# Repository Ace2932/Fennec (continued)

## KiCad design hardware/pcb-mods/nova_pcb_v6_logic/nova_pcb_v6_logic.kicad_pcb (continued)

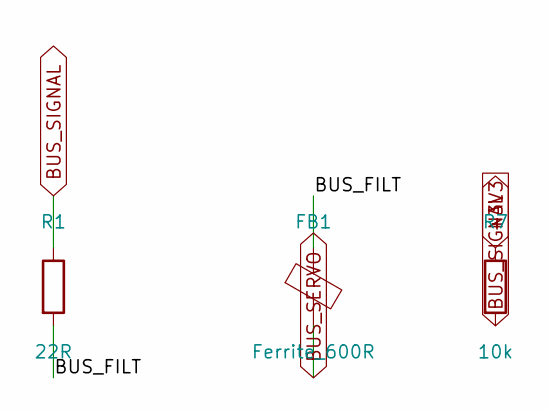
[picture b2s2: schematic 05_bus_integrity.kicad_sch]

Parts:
FB1: Ferrite_600R; L_0603_1608Metric
R1: 22R; R_0603_1608Metric
R7: 10k; R_0603_1608Metric

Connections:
+3V3: R7.1; also elsewhere on the board
/05 Bus Integrity/BUS_FILT: FB1.1, R1.2
BUS_SERVO: FB1.2; also elsewhere on the board
BUS_SIGNAL: R1.1, R7.2; also elsewhere on the board

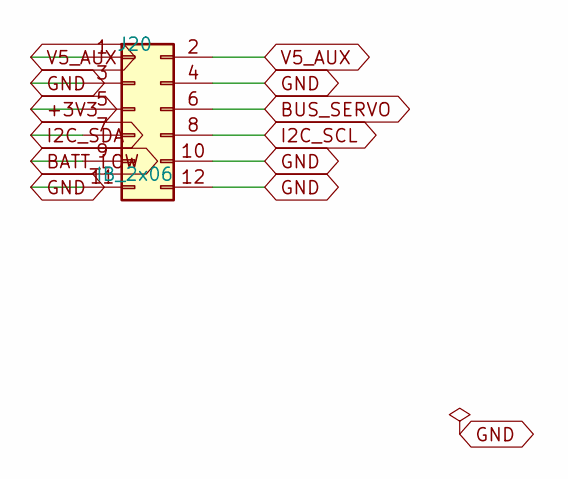
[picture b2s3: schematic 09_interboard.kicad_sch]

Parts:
J20: IB_2x06; IDC-Header_2x06_P2.54mm_Vertical

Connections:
+3V3: J20.5; also elsewhere on the board
BATT_LOW: J20.9; also elsewhere on the board
BUS_SERVO: J20.6; also elsewhere on the board
GND: J20.3, J20.4, J20.10, J20.11, J20.12; also elsewhere on the board
I2C_SCL: J20.8; also elsewhere on the board
I2C_SDA: J20.7; also elsewhere on the board
V5_AUX: J20.1, J20.2; also elsewhere on the board

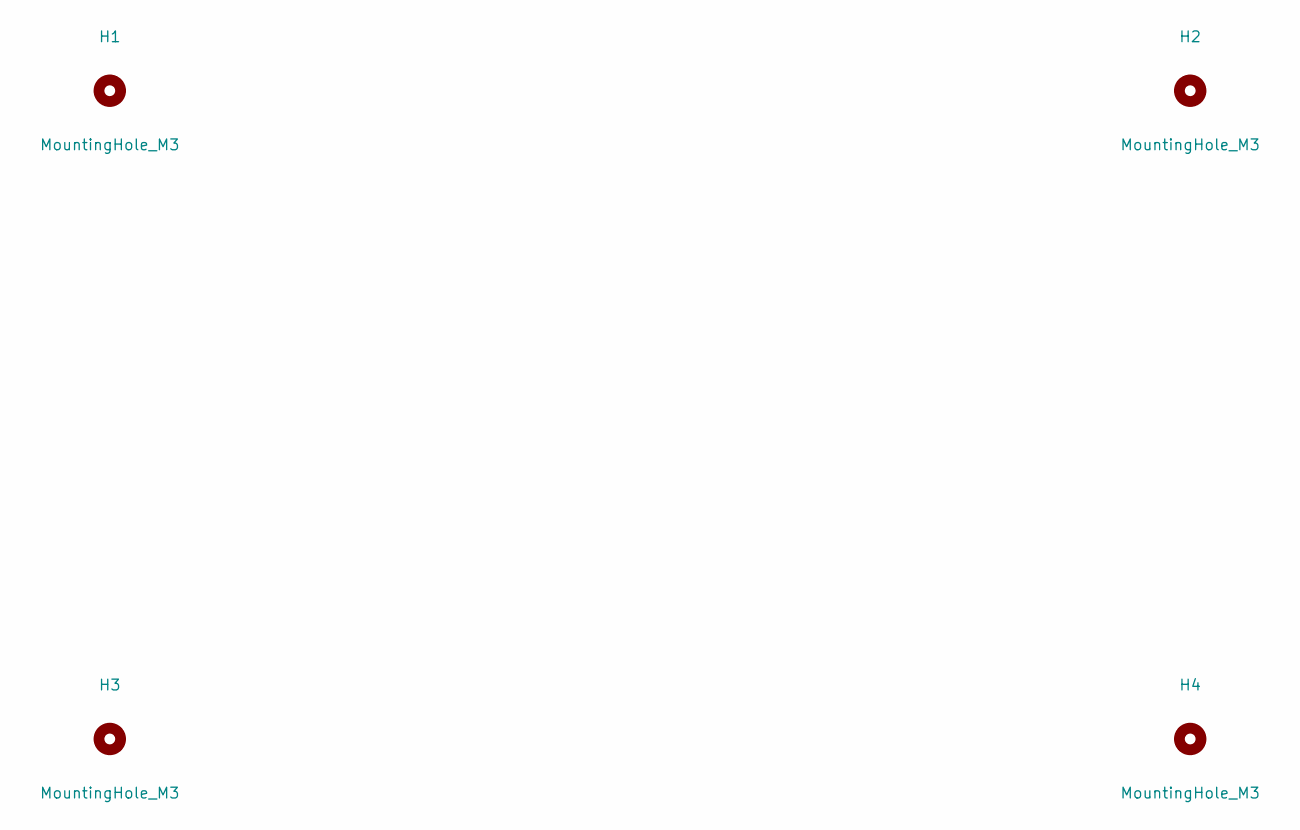
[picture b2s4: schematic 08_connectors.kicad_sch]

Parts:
H1, H2, H3, H4: MountingHole_M3; MountingHole_3.2mm_M3

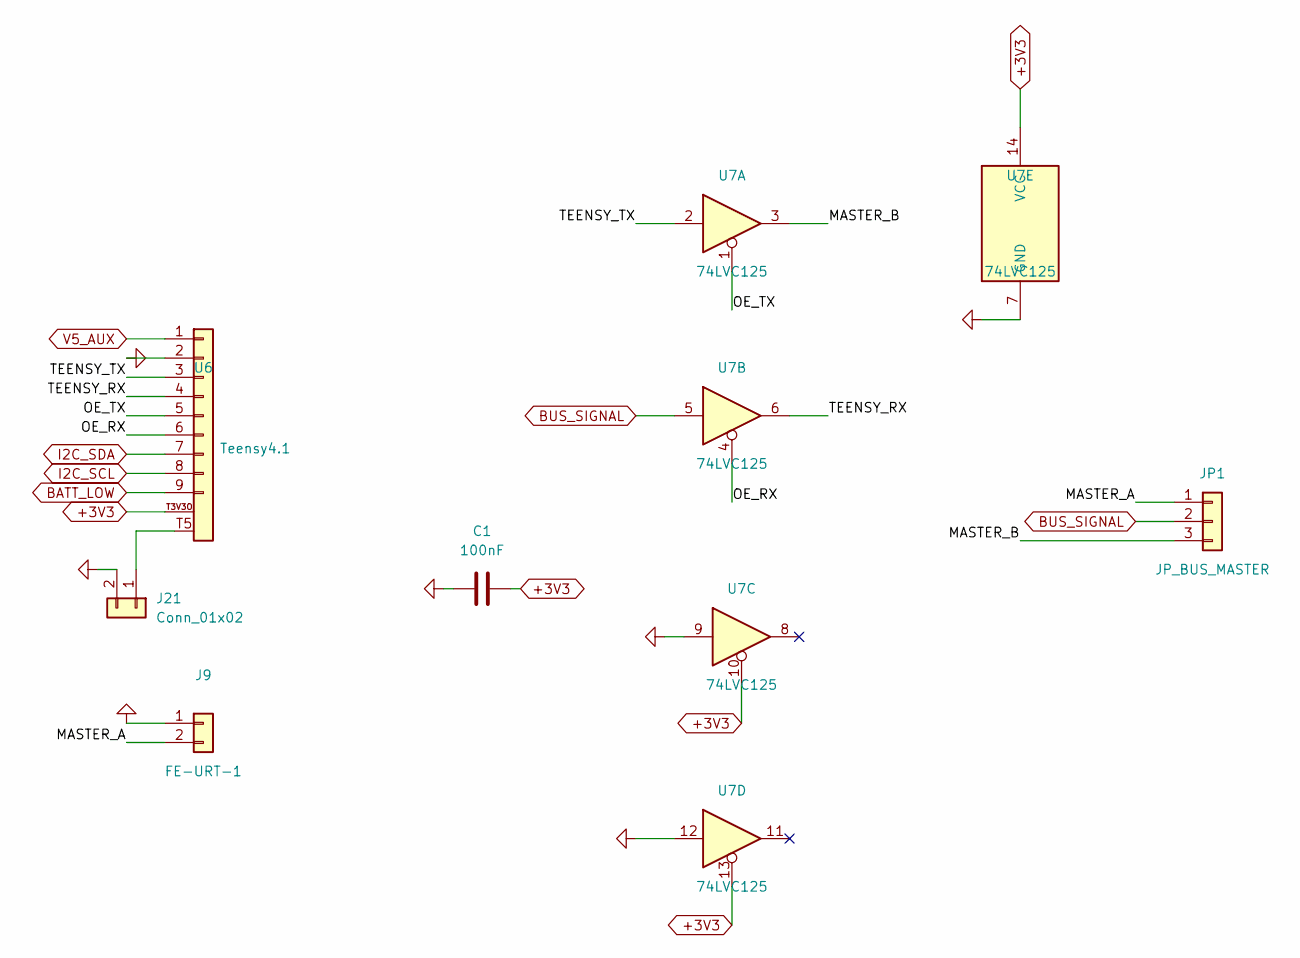
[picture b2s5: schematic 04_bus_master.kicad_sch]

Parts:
C1: 100nF; C_0603_1608Metric
J9: FE-URT-1; PinHeader_1x02_P2.54mm_Vertical
J21: Conn_01x02; PinHeader_1x02_P2.54mm_Vertical
JP1: JP_BUS_MASTER; PinHeader_1x03_P2.54mm_Vertical
U6: Teensy4.1; Teensy_4.1
U7: 74LVC125; SOIC-14_3.9x8.7mm_P1.27mm

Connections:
+3V3: C1.2, U6.T3V3O (3V3), U7.10, U7.13, U7.14 (VCC); also elsewhere on the board
/04 Bus Master (Pattern B)/MASTER_A: J9.2, JP1.1
/04 Bus Master (Pattern B)/MASTER_B: JP1.3, U7.3
/04 Bus Master (Pattern B)/OE_RX: U6.6, U7.4
/04 Bus Master (Pattern B)/OE_TX: U6.5, U7.1
/04 Bus Master (Pattern B)/TEENSY_RX: U6.4, U7.6
/04 Bus Master (Pattern B)/TEENSY_TX: U6.3, U7.2
BATT_LOW: U6.9; also elsewhere on the board
BUS_SIGNAL: JP1.2, U7.5; also elsewhere on the board
GND: C1.1, J9.1, J21.2, U6.2, U7.7 (GND), U7.9, U7.12; also elsewhere on the board
I2C_SCL: U6.8; also elsewhere on the board
I2C_SDA: U6.7; also elsewhere on the board
unnamed: J21.1, U6.T5
V5_AUX: U6.1; also elsewhere on the board

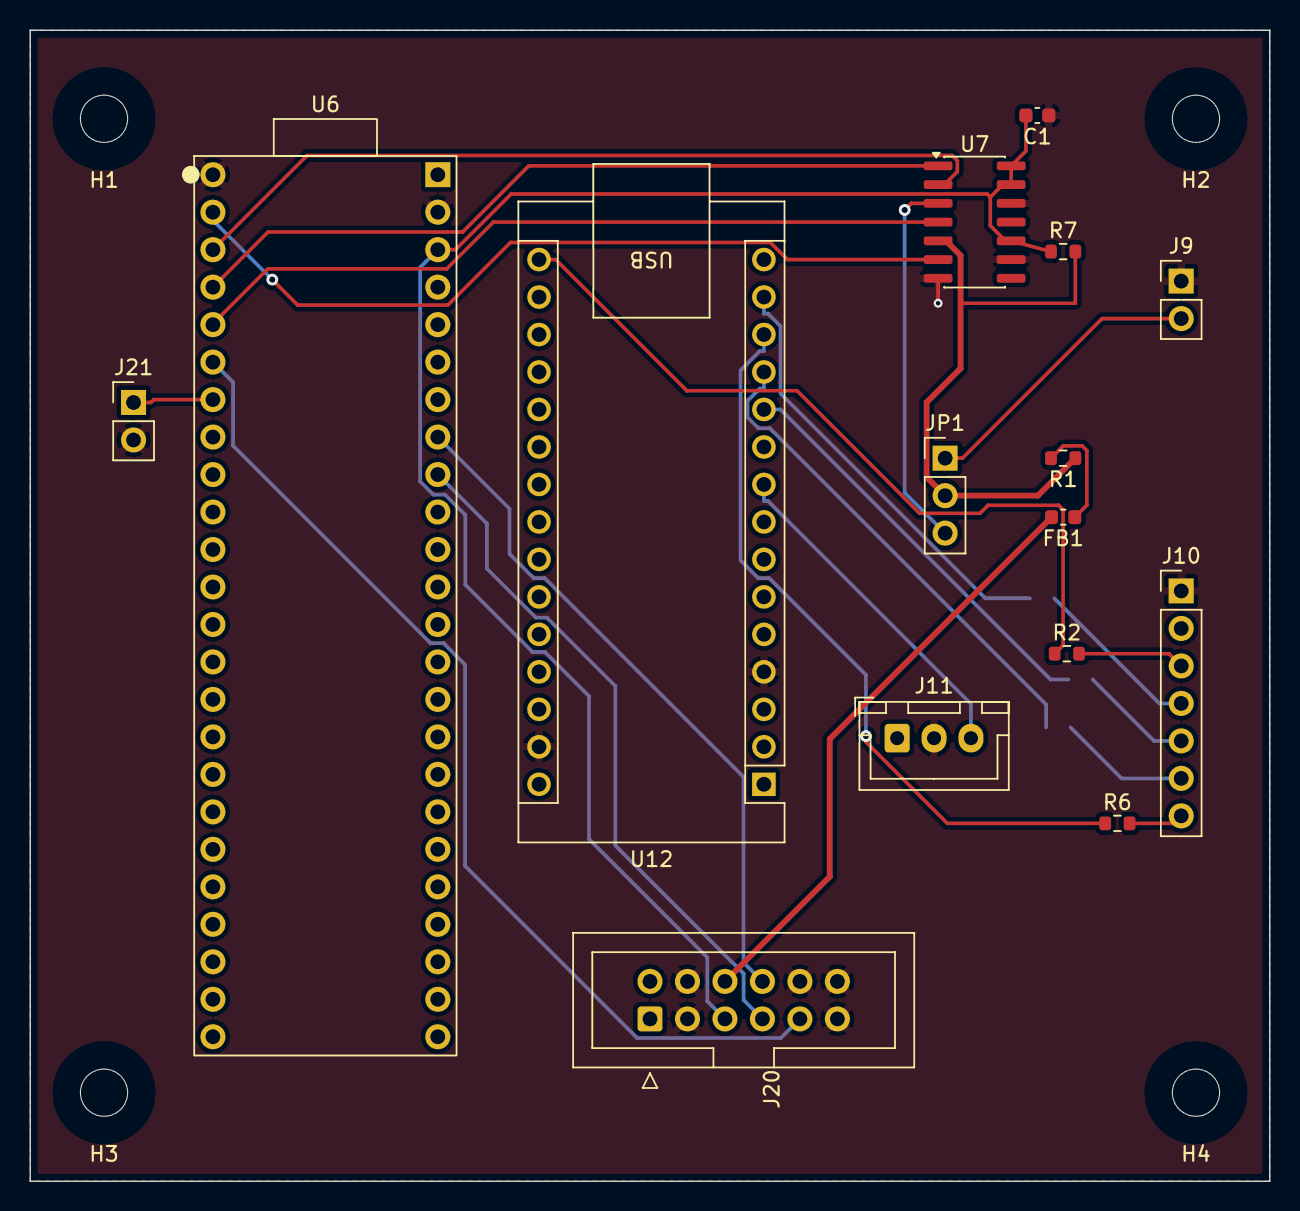
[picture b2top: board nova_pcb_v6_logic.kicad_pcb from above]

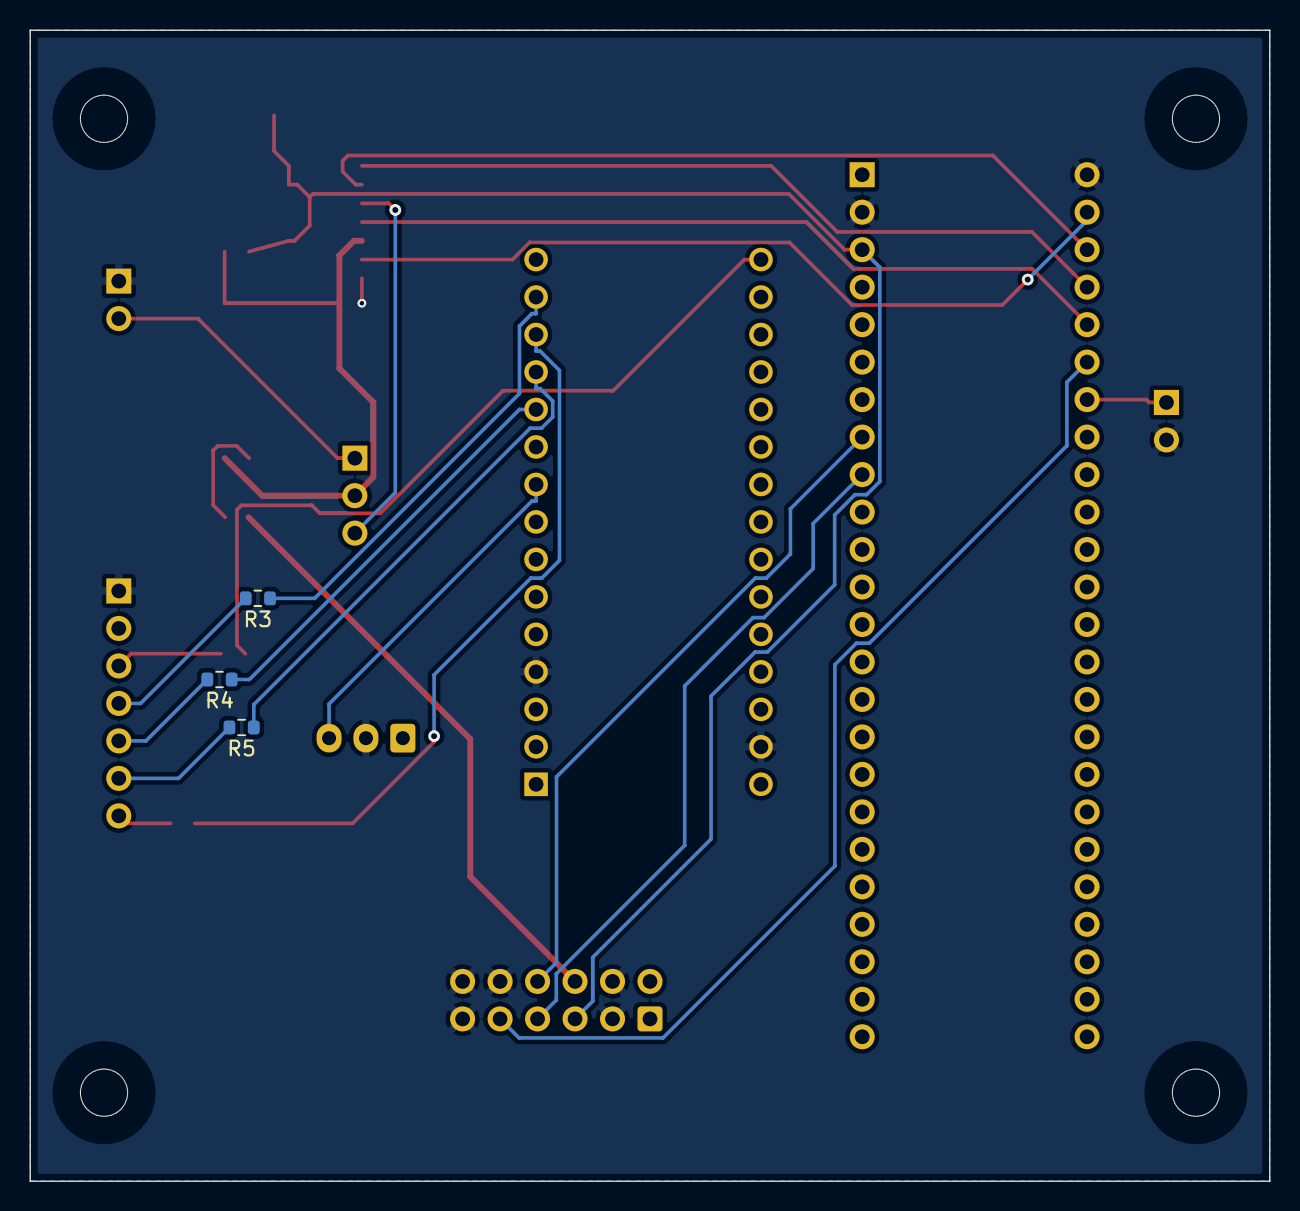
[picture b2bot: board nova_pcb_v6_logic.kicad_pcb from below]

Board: 4 copper layers, 84.0 x 78.0 mm, 22 parts (3 on the bottom side), 27 nets.

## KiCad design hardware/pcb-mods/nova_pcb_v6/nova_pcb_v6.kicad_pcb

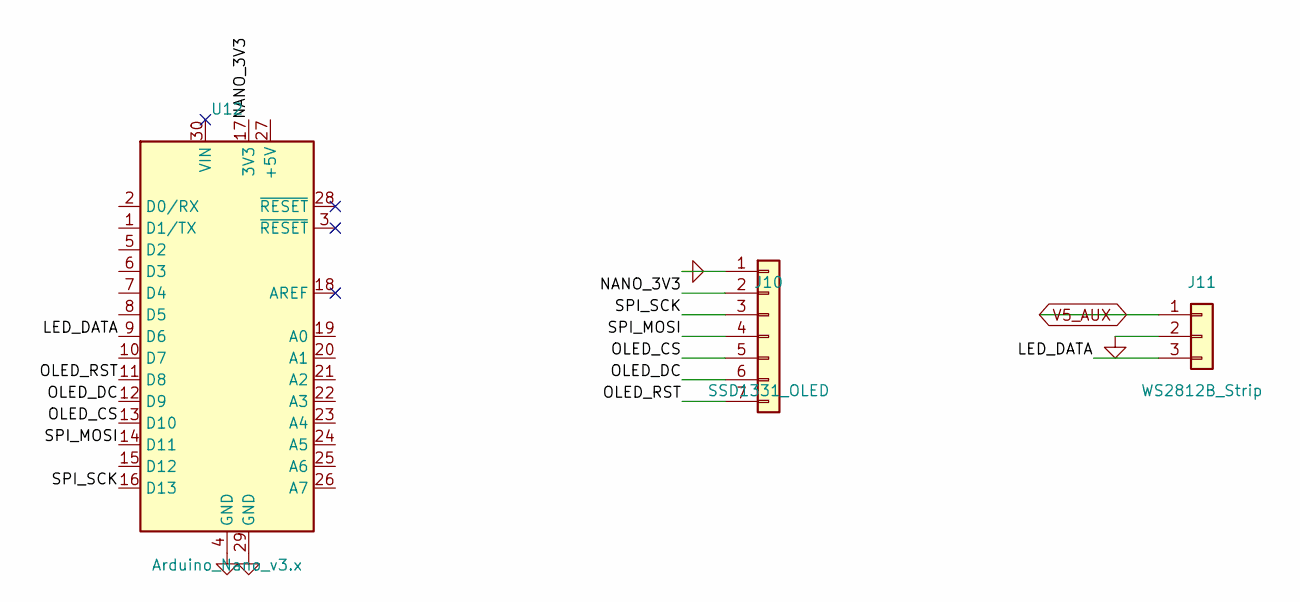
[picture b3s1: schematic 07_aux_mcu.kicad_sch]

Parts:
J10: SSD1331_OLED; PinHeader_1x07_P2.54mm_Vertical
J11: WS2812B_Strip; JST_XH_B3B-XH-A_1x03_P2.50mm_Vertical
U12: Arduino_Nano_v3.x; Arduino_Nano

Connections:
/07 Aux MCU + Peripherals/LED_DATA: J11.3, U12.9 (D6)
/07 Aux MCU + Peripherals/NANO_3V3: J10.2, U12.17 (3V3)
/07 Aux MCU + Peripherals/OLED_CS: J10.5, U12.13 (D10)
/07 Aux MCU + Peripherals/OLED_DC: J10.6, U12.12 (D9)
/07 Aux MCU + Peripherals/OLED_RST: J10.7, U12.11 (D8)
/07 Aux MCU + Peripherals/SPI_MOSI: J10.4, U12.14 (D11)
/07 Aux MCU + Peripherals/SPI_SCK: J10.3, U12.16 (D13)
GND: J10.1, J11.2, U12.4 (GND), U12.29 (GND); also elsewhere on the board
V5_AUX: J11.1; also elsewhere on the board

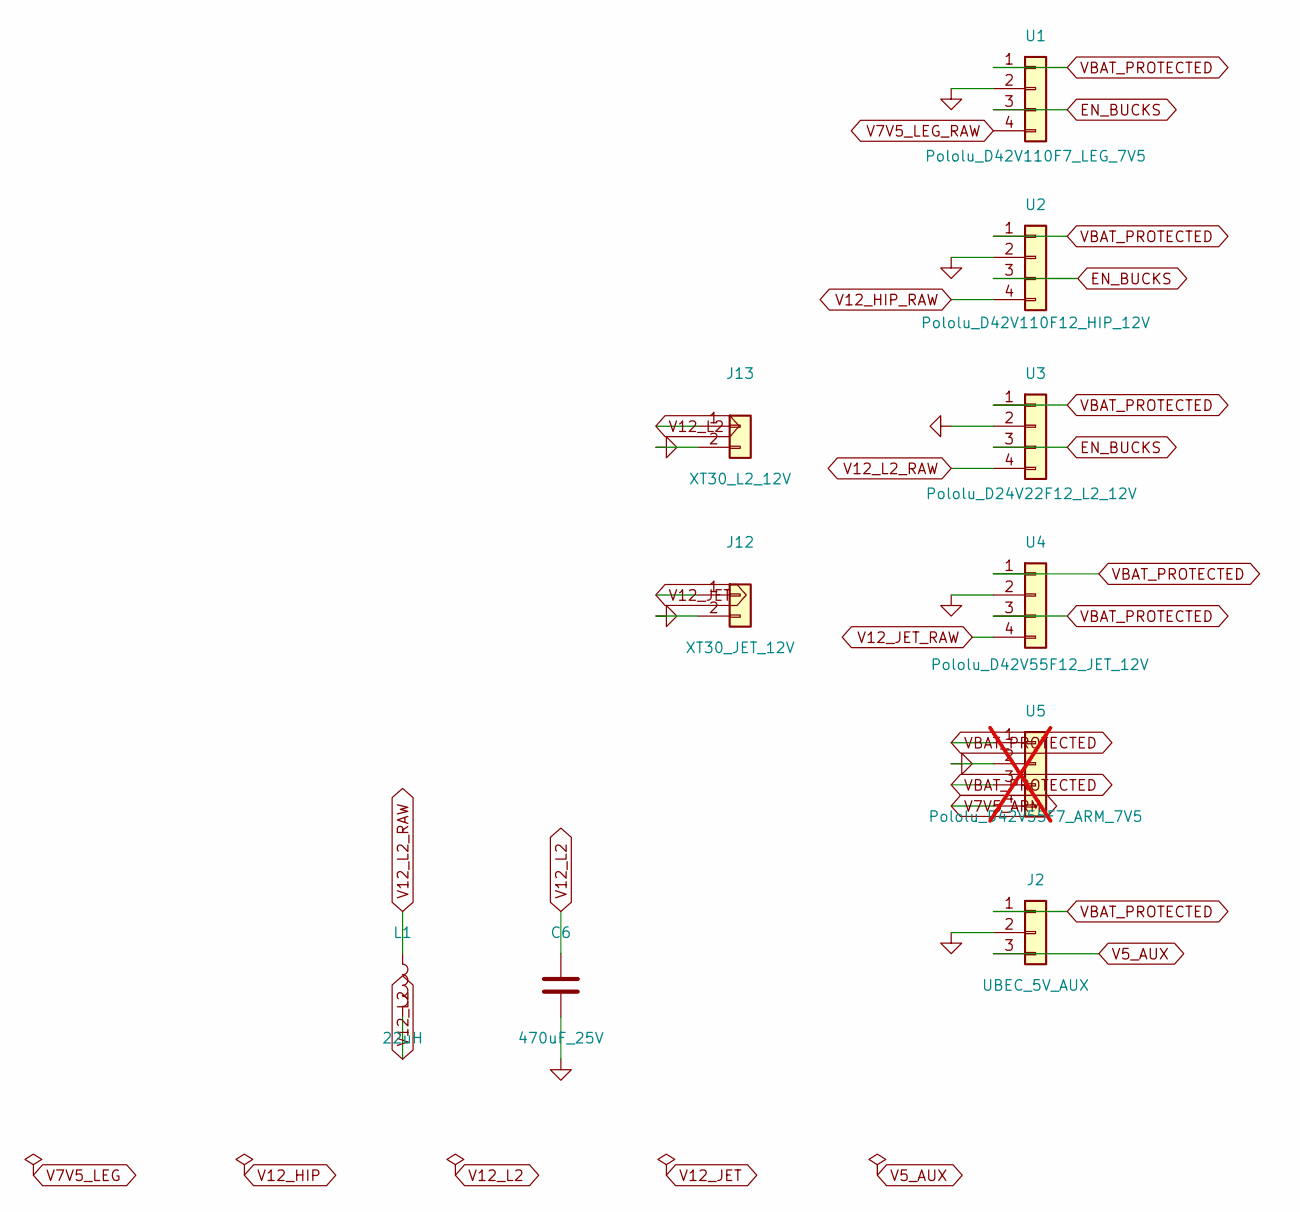
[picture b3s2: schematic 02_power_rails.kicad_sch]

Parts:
C6: 470uF_25V; CP_Radial_D10.0mm_P5.00mm
J2: UBEC_5V_AUX; PinHeader_1x03_P2.54mm_Vertical
J12: XT30_JET_12V; AMASS_XT30U-M_1x02_P5.0mm_Vertical
J13: XT30_L2_12V; AMASS_XT30U-M_1x02_P5.0mm_Vertical
L1: 22uH; L_12x12mm_H8mm
U1: Pololu_D42V110F7_LEG_7V5; Pololu_D42V110Fx
U2: Pololu_D42V110F12_HIP_12V; Pololu_D42V110Fx
U3: Pololu_D24V22F12_L2_12V; Pololu_D24V22Fx
U4: Pololu_D42V55F12_JET_12V; Pololu_D42V55Fx
U5: Pololu_D42V55F7_ARM_7V5; Pololu_D42V55Fx; not fitted

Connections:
EN_BUCKS: U1.3, U2.3, U3.3; also elsewhere on the board
GND: C6.2, J2.2, J12.2, J13.2, U1.2, U2.2, U3.2, U4.2, U5.2; also elsewhere on the board
V5_AUX: J2.3; also elsewhere on the board
V7V5_ARM: U5.4
V7V5_LEG_RAW: U1.4; also elsewhere on the board
V12_HIP_RAW: U2.4; also elsewhere on the board
V12_JET: J12.1; also elsewhere on the board
V12_JET_RAW: U4.4; also elsewhere on the board
V12_L2: C6.1, J13.1, L1.2
V12_L2_RAW: L1.1, U3.4
VBAT_PROTECTED: J2.1, U1.1, U2.1, U3.1, U4.1, U4.3, U5.1, U5.3; also elsewhere on the board

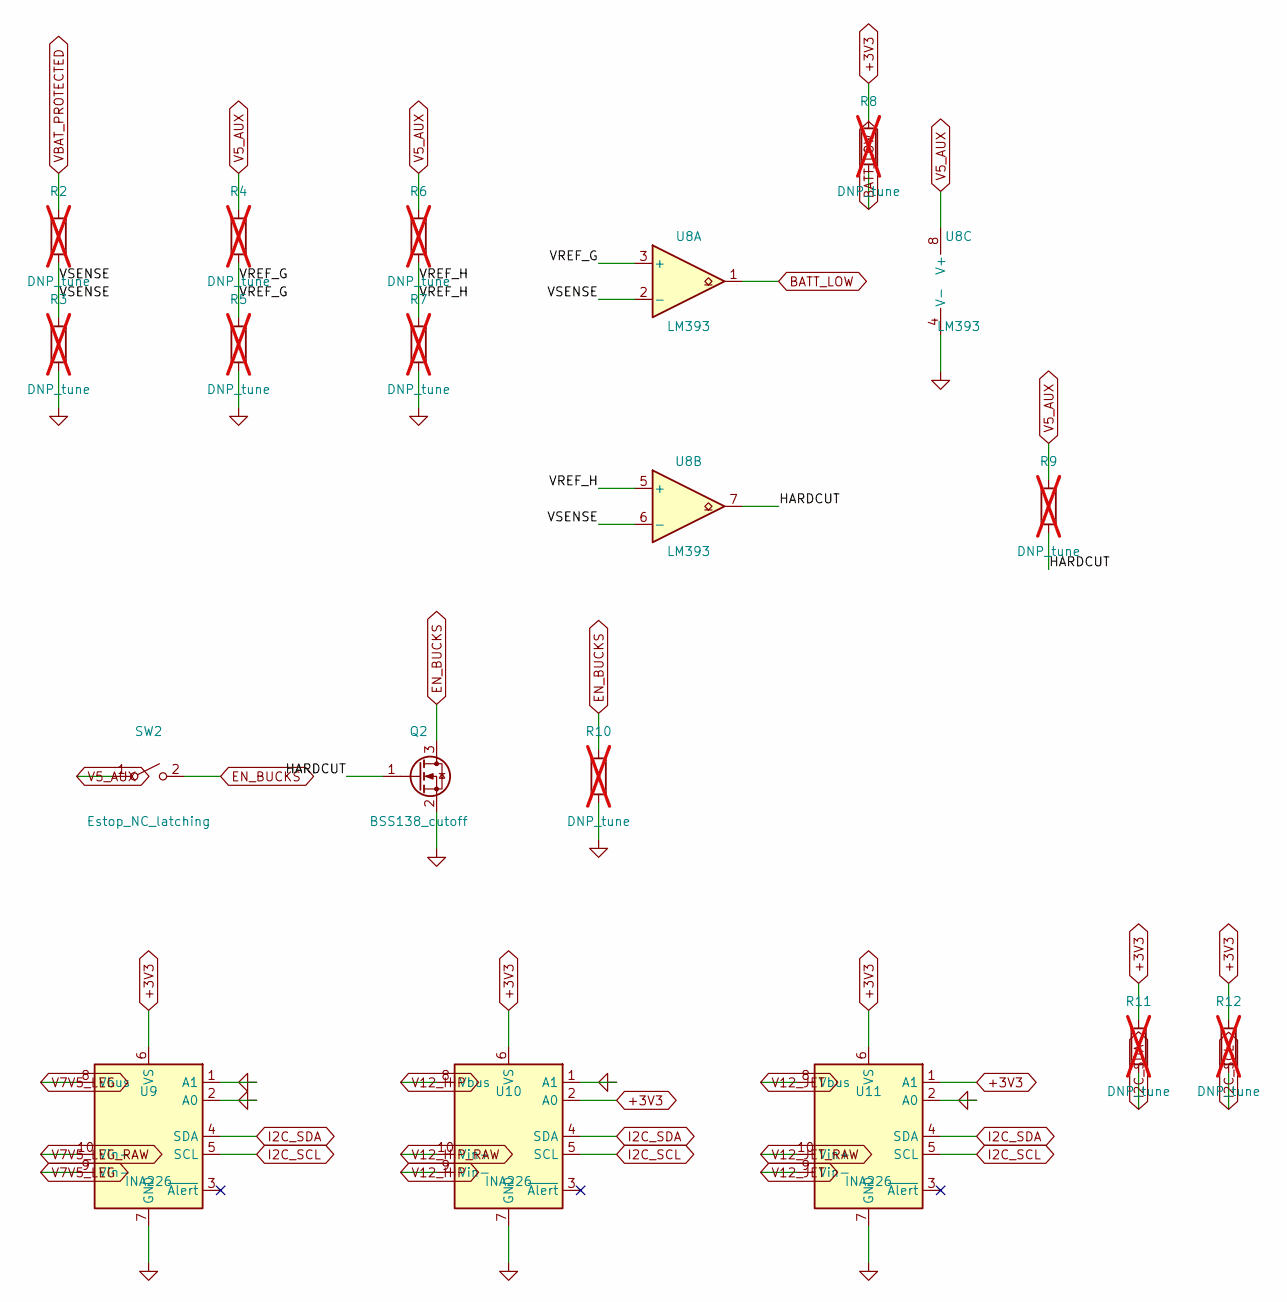
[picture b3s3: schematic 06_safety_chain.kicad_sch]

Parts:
Q2: BSS138_cutoff; SOT-23
R2, R3, R4, R5, R6, R7, R8, R9, R10, R11, R12: DNP_tune; R_0603_1608Metric; not fitted
SW2: Estop_NC_latching; TerminalBlock_Philmore_TB132_1x02_P5.00mm_Horizontal
U8: LM393; SOIC-8_3.9x4.9mm_P1.27mm
U9, U10, U11: INA226; INA226_Module_Breakout

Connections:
+3V3: R8.1, R11.1, R12.1, U9.6 (VS), U10.2 (A0), U10.6 (VS), U11.1 (A1), U11.6 (VS); also elsewhere on the board
/06 Safety Chain/HARDCUT: Q2.1 (G), R9.2, U8.7
/06 Safety Chain/VREF_G: R4.2, R5.1, U8.3 (+)
/06 Safety Chain/VREF_H: R6.2, R7.1, U8.5 (+)
/06 Safety Chain/VSENSE: R2.2, R3.1, U8.2 (-), U8.6 (-)
BATT_LOW: R8.2, U8.1; also elsewhere on the board
EN_BUCKS: Q2.3 (D), R10.1, SW2.2 (B); also elsewhere on the board
GND: Q2.2 (S), R3.2, R5.2, R7.2, R10.2, U8.4 (V-), U9.1 (A1), U9.2 (A0), U9.7 (GND), U10.1 (A1), U10.7 (GND), U11.2 (A0), U11.7 (GND); also elsewhere on the board
I2C_SCL: R12.2, U9.5 (SCL), U10.5 (SCL), U11.5 (SCL); also elsewhere on the board
I2C_SDA: R11.2, U9.4 (SDA), U10.4 (SDA), U11.4 (SDA); also elsewhere on the board
V5_AUX: R4.1, R6.1, R9.1, SW2.1 (A), U8.8 (V+); also elsewhere on the board
V7V5_LEG: U9.8 (Vbus), U9.9 (Vin-); also elsewhere on the board
V7V5_LEG_RAW: U9.10 (Vin+); also elsewhere on the board
V12_HIP: U10.8 (Vbus), U10.9 (Vin-); also elsewhere on the board
V12_HIP_RAW: U10.10 (Vin+); also elsewhere on the board
V12_JET: U11.8 (Vbus), U11.9 (Vin-); also elsewhere on the board
V12_JET_RAW: U11.10 (Vin+); also elsewhere on the board
VBAT_PROTECTED: R2.1; also elsewhere on the board

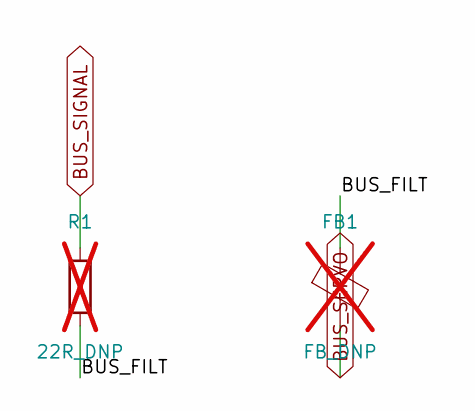
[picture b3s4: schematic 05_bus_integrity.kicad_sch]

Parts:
FB1: FB_DNP; L_0603_1608Metric; not fitted
R1: 22R_DNP; R_0603_1608Metric; not fitted

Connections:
/05 Bus Integrity/BUS_FILT: FB1.1, R1.2
BUS_SERVO: FB1.2; also elsewhere on the board
BUS_SIGNAL: R1.1; also elsewhere on the board

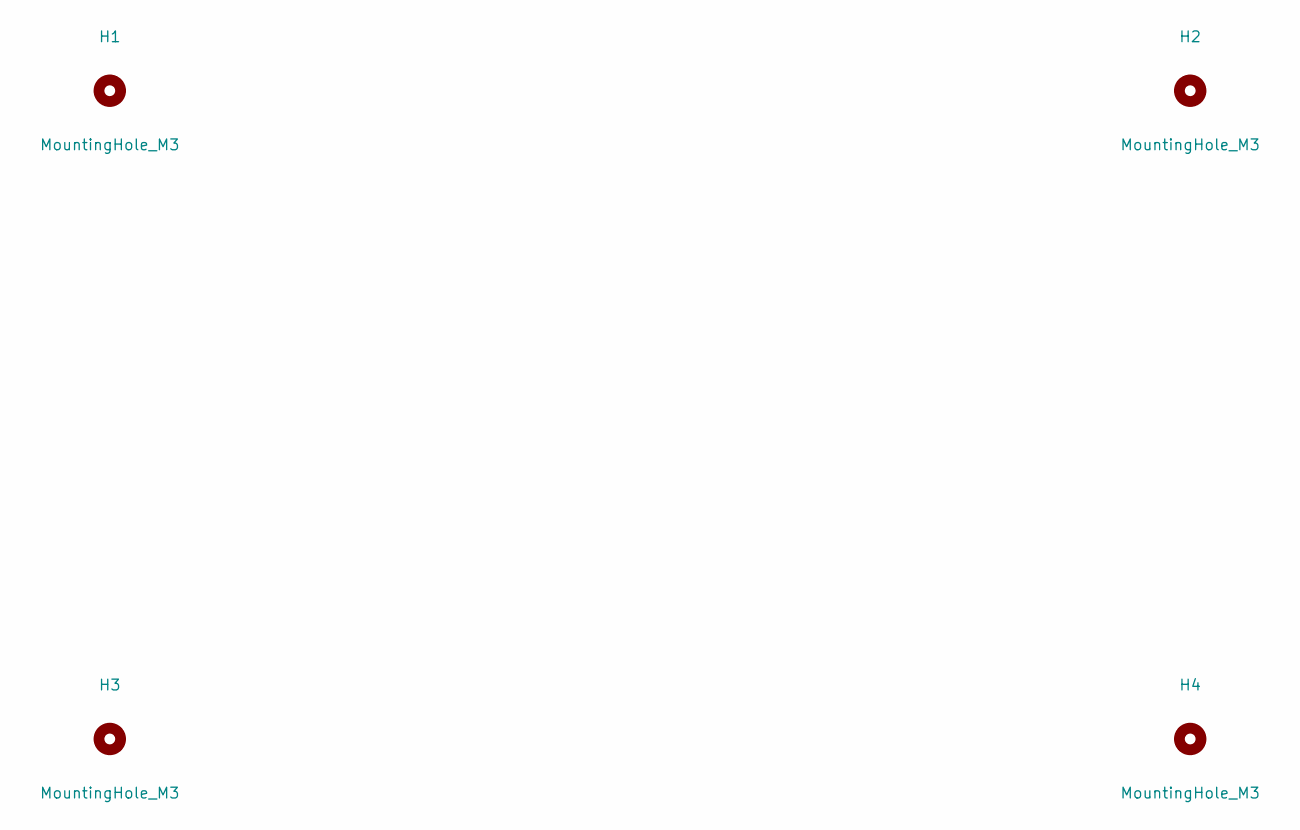
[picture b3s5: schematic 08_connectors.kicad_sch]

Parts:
H1, H2, H3, H4: MountingHole_M3; MountingHole_3.2mm_M3

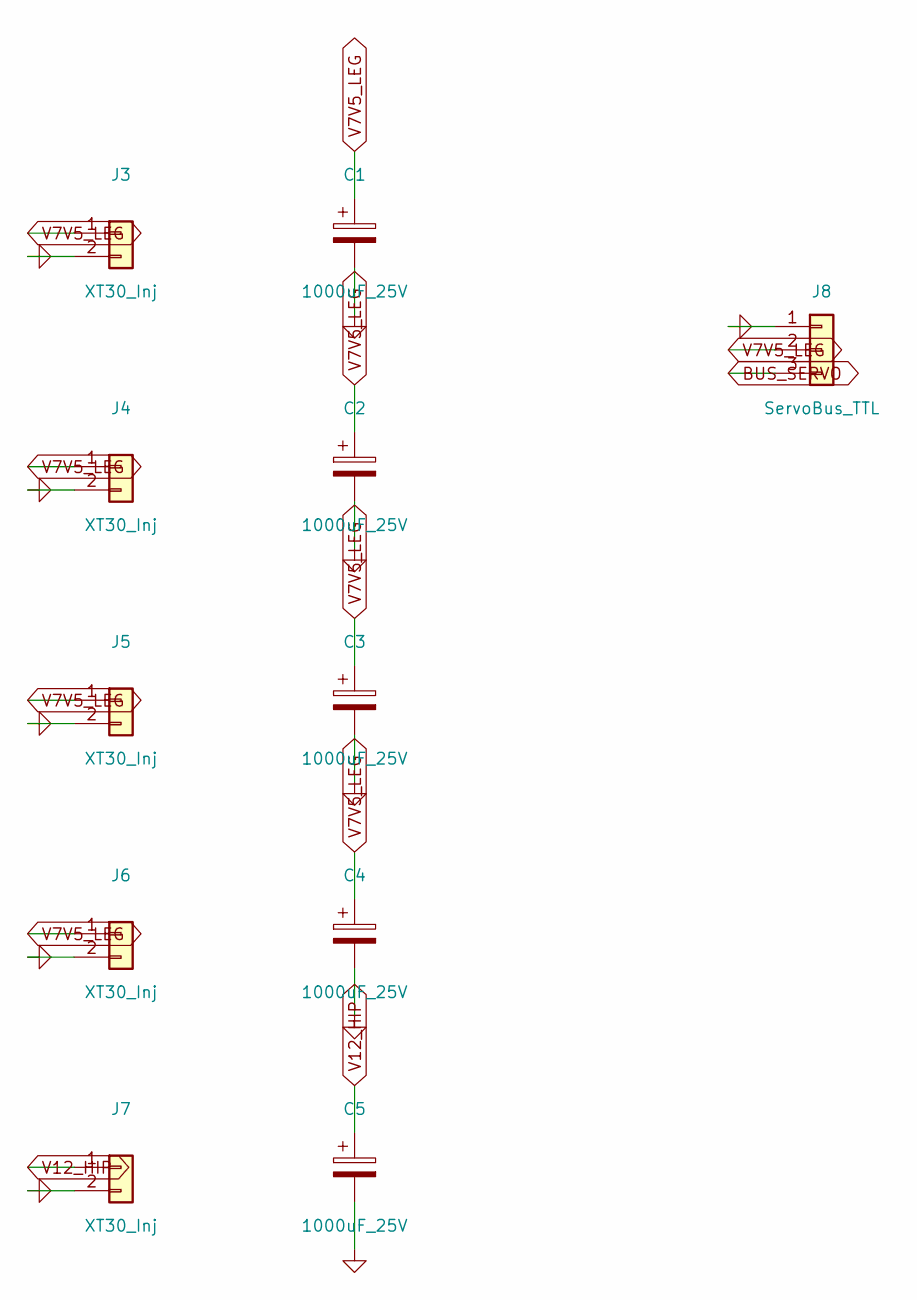
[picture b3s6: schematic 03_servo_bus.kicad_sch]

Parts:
C1, C2, C3, C4, C5: 1000uF_25V; CP_Radial_D12.5mm_P5.00mm
J3, J4, J5, J6, J7: XT30_Inj; AMASS_XT30U-M_1x02_P5.0mm_Vertical
J8: ServoBus_TTL; JST_XH_B3B-XH-A_1x03_P2.50mm_Vertical

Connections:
BUS_SERVO: J8.3; also elsewhere on the board
GND: C1.2, C2.2, C3.2, C4.2, C5.2, J3.2, J4.2, J5.2, J6.2, J7.2, J8.1; also elsewhere on the board
V7V5_LEG: C1.1, C2.1, C3.1, C4.1, J3.1, J4.1, J5.1, J6.1, J8.2; also elsewhere on the board
V12_HIP: C5.1, J7.1; also elsewhere on the board

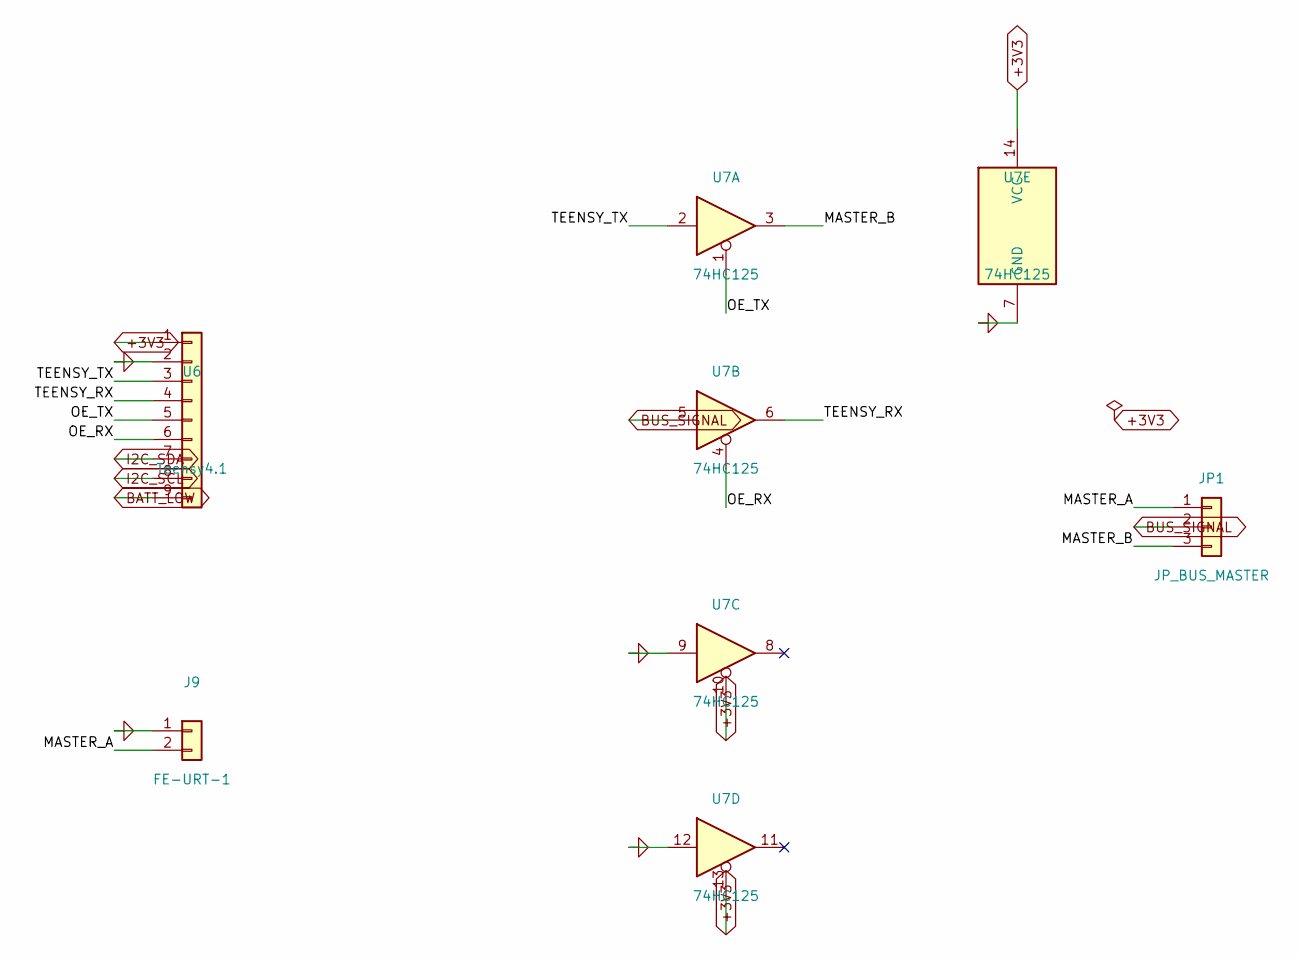
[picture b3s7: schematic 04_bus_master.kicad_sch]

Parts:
J9: FE-URT-1; PinHeader_1x02_P2.54mm_Vertical
JP1: JP_BUS_MASTER; PinHeader_1x03_P2.54mm_Vertical
U6: Teensy4.1; Teensy_4.1
U7: 74HC125; SOIC-14_3.9x8.7mm_P1.27mm

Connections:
+3V3: U6.1, U7.10, U7.13, U7.14 (VCC); also elsewhere on the board
/04 Bus Master (Pattern B)/MASTER_A: J9.2, JP1.1
/04 Bus Master (Pattern B)/MASTER_B: JP1.3, U7.3
/04 Bus Master (Pattern B)/OE_RX: U6.6, U7.4
/04 Bus Master (Pattern B)/OE_TX: U6.5, U7.1
/04 Bus Master (Pattern B)/TEENSY_RX: U6.4, U7.6
/04 Bus Master (Pattern B)/TEENSY_TX: U6.3, U7.2
BATT_LOW: U6.9; also elsewhere on the board
BUS_SIGNAL: JP1.2, U7.5; also elsewhere on the board
GND: J9.1, U6.2, U7.7 (GND), U7.9, U7.12; also elsewhere on the board
I2C_SCL: U6.8; also elsewhere on the board
I2C_SDA: U6.7; also elsewhere on the board

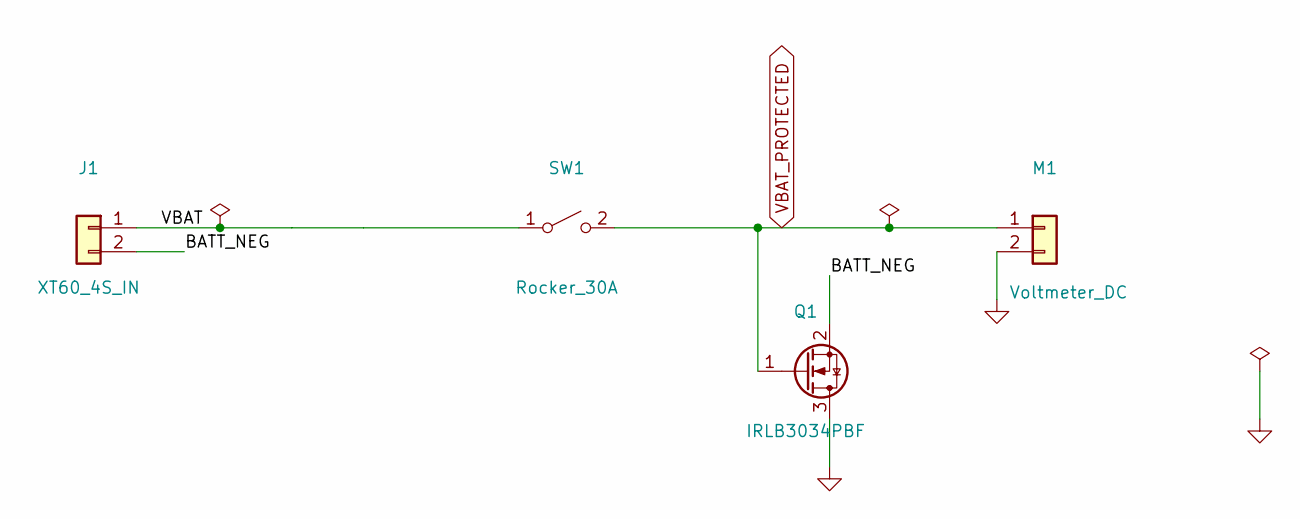
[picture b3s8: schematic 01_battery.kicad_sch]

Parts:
J1: XT60_4S_IN; AMASS_XT60-M_1x02_P7.20mm_Vertical
M1: Voltmeter_DC; PinHeader_1x02_P2.54mm_Vertical
Q1: IRLB3034PBF; TO-220-3_Vertical
SW1: Rocker_30A; TerminalBlock_Philmore_TB132_1x02_P5.00mm_Horizontal

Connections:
/01 Battery Input + Reverse Protection/BATT_NEG: J1.2, Q1.2 (S)
/01 Battery Input + Reverse Protection/VBAT: J1.1, SW1.1 (A)
GND: M1.2, Q1.3 (D); also elsewhere on the board
VBAT_PROTECTED: M1.1, Q1.1 (G), SW1.2 (B); also elsewhere on the board

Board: 4 copper layers, 55 parts (0 on the bottom side), 38 nets, no tracks yet.

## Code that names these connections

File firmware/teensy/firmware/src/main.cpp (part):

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// ---------------- Pinout ----------------
// Pin numbers reconciled to nova_pcb_v6_logic board routing 2026-06-14.
// UART1 (Serial1) → 74LVC125 → Feetech bus
constexpr uint8_t BUS_RX_PIN     = 0;   // Serial1 RX (board: U6 pad TEENSY_RX → pin 0)
constexpr uint8_t BUS_TX_PIN     = 1;   // Serial1 TX (board: U6 pad TEENSY_TX → pin 1)
constexpr uint8_t BUS_OE_TX_PIN  = 2;   // 74LVC125 OE̅ for TX gate (ACTIVE-LOW: LOW = enable TX)
constexpr uint8_t BUS_OE_RX_PIN  = 3;   // 74LVC125 OE̅ for RX gate (ACTIVE-LOW: LOW = enable RX)
// I2C0 (Wire) — INA226 ×3, ×4 with NOVA_INA226_L2 (on in the default build)
constexpr uint8_t I2C_SDA_PIN    = 18;
constexpr uint8_t I2C_SCL_PIN    = 19;
// Safety GPIO
constexpr uint8_t ESTOP_PIN       = 5;   // E-stop NC contact (J21) w/ INPUT_PULLUP. NC closed = LOW idle;
                                         // pressed OR wire-break/unplug = HIGH (fail-safe)
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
